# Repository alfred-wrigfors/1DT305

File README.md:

# 1DT305
Summer 2025 - Applied IoT

> [!NOTE]
> I, the author, have multiple years of experience in both embedded hardware design and software development. The level of complexity of this project is not reasonable for a beginner IoT-project!

## Introduction
With family living close to the Vikhög marina, there is the constant question wether or not the condition in/around the marina is appropriate for going swimming. It is mostly the water temperature and levels of wind that are of interest. Insight into the conditions in the marina would greatly increase the likelihood of spontaneous and enjoyable swims, while also helping to avoid unpleasant surprises - such as unexpected cold water or strong winds. Rather than relying on regional forecasts, a localized monitoring system would offer a much more accurate and timely solution.

This project aims to provide current and up-to-date temperature readings, for both the water and air, accross the marina and an overall wind speed and heading reading. The goal is to distribute 2-4 battery- and solar powered sensor-stations at the most popular areas for going swimming, communicating wirelessly with a base-station that is connected to the internet and sending the data to a remote server that provides the information (both current and historic) in a simple and intuitive web-interface.

## Goals and constraints
Some overall goals for the project:
 - Server / web interface containerized to run in a Docker container.
 - The base station and the mobile units should be electronically identical.
 - Hardware designed to be fully assebled by the PCB fab.
 - Be able to sustain one month (31 days) of operation without recharging the unit manually.
 - WiFi enabled.
 - USB-C (programming, serial debugging and power).
 - Temperature sensor (air and water)
 - Humidity sensor.
 - Light sensor (photoresisotr / phototransistor).
 - (Pressure sensor) [OPTIONAL]

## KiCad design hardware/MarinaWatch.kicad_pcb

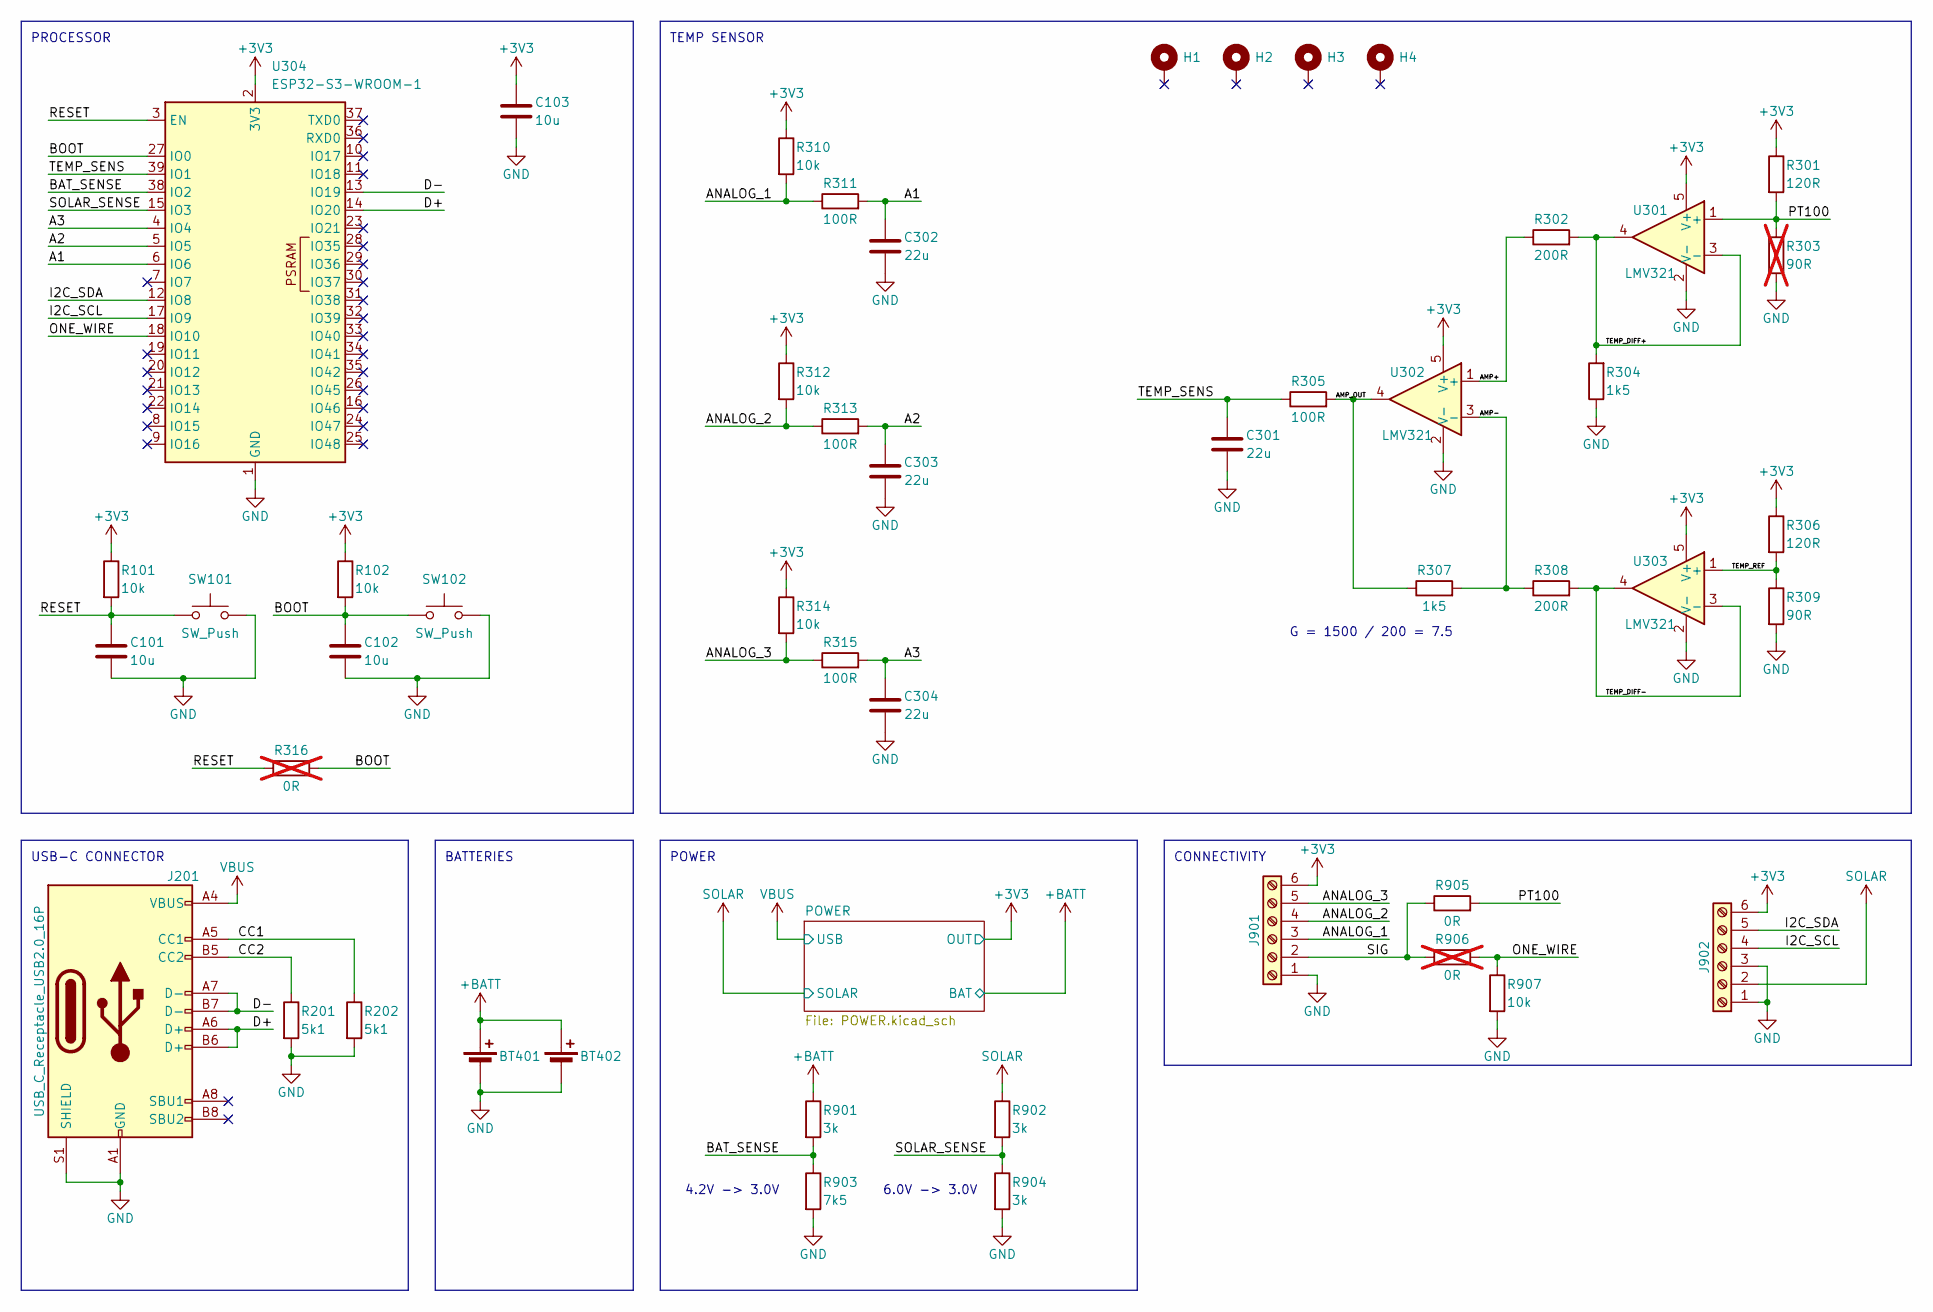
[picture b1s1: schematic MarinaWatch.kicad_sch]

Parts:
BT401, BT402: Battery_Cell; 18650
C101, C102, C103: 10u; C_0603_1608Metric_Pad1.08x0.95mm_HandSolder
C301, C302, C303, C304: 22u; C_0603_1608Metric_Pad1.08x0.95mm_HandSolder
H1, H2, H3, H4: MountingHole_Pad; MountingHole_3.2mm_M3_DIN965_Pad
J201: USB_C_Receptacle_USB2.0_16P; USB_C_Receptacle_G-Switch_GT-USB-7010ASV
J901, J902: Screw_Terminal_01x06; THT_SCREW_01x06_P5.08mm
R101, R102, R310, R312, R314, R907: 10k; R_0603_1608Metric_Pad0.98x0.95mm_HandSolder
R201, R202: 5k1; R_0603_1608Metric_Pad0.98x0.95mm_HandSolder
R301, R306: 120R; R_0603_1608Metric_Pad0.98x0.95mm_HandSolder
R302, R308: 200R; R_0603_1608Metric_Pad0.98x0.95mm_HandSolder
R303: 90R; R_0603_1608Metric_Pad0.98x0.95mm_HandSolder; not fitted
R304, R307: 1k5; R_0603_1608Metric_Pad0.98x0.95mm_HandSolder
R305, R311, R313, R315: 100R; R_0603_1608Metric_Pad0.98x0.95mm_HandSolder
R309: 90R; R_0603_1608Metric_Pad0.98x0.95mm_HandSolder
R316, R906: 0R; R_0603_1608Metric_Pad0.98x0.95mm_HandSolder; not fitted
R901, R902, R904: 3k; R_0603_1608Metric_Pad0.98x0.95mm_HandSolder
R903: 7k5; R_0603_1608Metric_Pad0.98x0.95mm_HandSolder
R905: 0R; R_0603_1608Metric_Pad0.98x0.95mm_HandSolder
SW101, SW102: SW_Push; BUTTON_SMD_3x4mm
U301, U302, U303: LMV321; SOT-23-5
U304: ESP32-S3-WROOM-1

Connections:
+3V3: C103.1, J901.6, J902.6, R101.1, R102.1, R301.1, R306.1, R310.1, R312.1, R314.1, U301.5 (V+), U302.5 (V+), U303.5 (V+), U304.2 (3V3); also elsewhere on the board
+BATT: BT401.1 (+), BT402.1 (+), R901.1; also elsewhere on the board
/A1: C302.1, R311.2, U304.6 (IO6)
/A2: C303.1, R313.2, U304.5 (IO5)
/A3: C304.1, R315.2, U304.4 (IO4)
/AMP+: R302.1, U302.1 (+)
/AMP-: R307.2, R308.1, U302.3 (-)
/AMP_OUT: R305.2, R307.1, U302.4
/ANALOG_1: J901.3, R310.2, R311.1
/ANALOG_2: J901.4, R312.2, R313.1
/ANALOG_3: J901.5, R314.2, R315.1
/BAT_SENSE: R901.2, R903.1, U304.38 (IO2)
/BOOT: C102.1, R102.2, R316.2, SW102.1, U304.27 (IO0)
/CC1: J201.A5 (CC1), R202.1
/CC2: J201.B5 (CC2), R201.1
/D+: J201.A6 (D+), J201.B6 (D+), U304.14 (IO20)
/D-: J201.A7 (D-), J201.B7 (D-), U304.13 (IO19)
/I2C_SCL: J902.4, U304.17 (IO9)
/I2C_SDA: J902.5, U304.12 (IO8)
/ONE_WIRE: R906.2, R907.1, U304.18 (IO10)
/PT100: R301.2, R303.1, R905.2, U301.1 (+)
/RESET: C101.1, R101.2, R316.1, SW101.1, U304.3 (EN)
/SIG: J901.2, R905.1, R906.1
/SOLAR_SENSE: R902.2, R904.1, U304.15 (IO3)
/TEMP_DIFF+: R302.2, R304.2, U301.3 (-), U301.4
/TEMP_DIFF-: R308.2, U303.3 (-), U303.4
/TEMP_REF: R306.2, R309.1, U303.1 (+)
/TEMP_SENS: C301.1, R305.1, U304.39 (IO1)
GND: BT401.2 (-), BT402.2 (-), C101.2, C102.2, C103.2, C301.2, C302.2, C303.2, C304.2, J201.A1 (GND), J201.A12 (GND), J201.B1 (GND), J201.B12 (GND), J201.S1 (SHIELD), J901.1, J902.1, J902.3, R201.2, R202.2, R303.2, R304.1, R309.2, R903.2, R904.2, R907.2, SW101.2, SW102.2, U301.2 (V-), U302.2 (V-), U303.2 (V-), U304.1 (GND), U304.40 (GND), U304.41 (GND); also elsewhere on the board
SOLAR: J902.2, R902.1; also elsewhere on the board
VBUS: J201.A4 (VBUS), J201.A9 (VBUS), J201.B4 (VBUS), J201.B9 (VBUS); also elsewhere on the board

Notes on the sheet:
BATTERIES
4.2V -> 3.0V
USB-C CONNECTOR
TEMP SENSOR
POWER
CONNECTIVITY
6.0V -> 3.0V
PROCESSOR
G = 1500 / 200 = 7.5

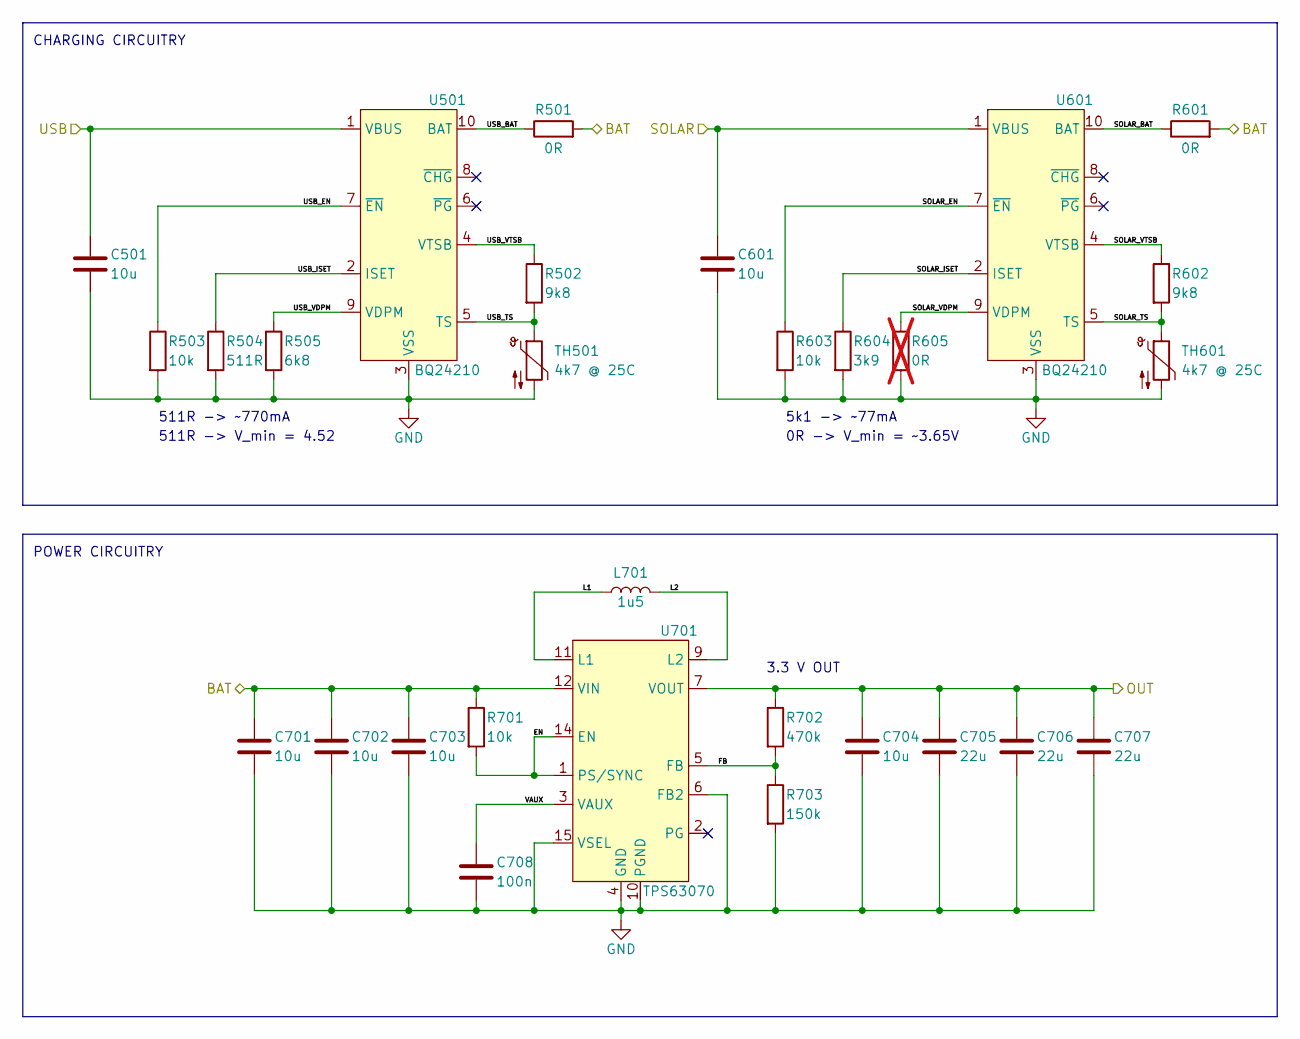
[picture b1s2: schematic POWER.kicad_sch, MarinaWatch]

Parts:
C501, C601, C701, C702, C703, C704: 10u; C_0603_1608Metric_Pad1.08x0.95mm_HandSolder
C705, C706, C707: 22u; C_0603_1608Metric_Pad1.08x0.95mm_HandSolder
C708: 100n; C_0603_1608Metric_Pad1.08x0.95mm_HandSolder
L701: 1u5; L_Wurth_WE-LQSH-2010
R501, R601: 0R; R_0603_1608Metric_Pad0.98x0.95mm_HandSolder
R502, R602: 9k8; R_0603_1608Metric_Pad0.98x0.95mm_HandSolder
R503, R603, R701: 10k; R_0603_1608Metric_Pad0.98x0.95mm_HandSolder
R504: 511R; R_0603_1608Metric_Pad0.98x0.95mm_HandSolder
R505: 6k8; R_0603_1608Metric_Pad0.98x0.95mm_HandSolder
R604: 3k9; R_0603_1608Metric_Pad0.98x0.95mm_HandSolder
R605: 0R; R_0603_1608Metric_Pad0.98x0.95mm_HandSolder; not fitted
R702: 470k; R_0603_1608Metric_Pad0.98x0.95mm_HandSolder
R703: 150k; R_0603_1608Metric_Pad0.98x0.95mm_HandSolder
TH501, TH601: 4k7 @ 25C; R_0603_1608Metric_Pad0.98x0.95mm_HandSolder
U501, U601: BQ24210; WSON-10
U701: TPS63070; VQFN-3.0x2.5

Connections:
+3V3: C704.1, C705.1, C706.1, C707.1, R702.1, U701.7 (VOUT), U701.8 (VOUT); also elsewhere on the board
+BATT: C701.1, C702.1, C703.1, R501.2, R601.2, R701.1, U701.12 (VIN), U701.13 (VIN); also elsewhere on the board
/POWER/EN: R701.2, U701.1 (PS/SYNC), U701.14 (EN)
/POWER/FB: R702.2, R703.1, U701.5 (FB)
/POWER/L1: L701.1, U701.11 (L1)
/POWER/L2: L701.2, U701.9 (L2)
/POWER/SOLAR_BAT: R601.1, U601.10 (BAT)
/POWER/SOLAR_EN: R603.1, U601.7 (~EN)
/POWER/SOLAR_ISET: R604.1, U601.2 (ISET)
/POWER/SOLAR_TS: R602.2, TH601.1, U601.5 (TS)
/POWER/SOLAR_VDPM: R605.1, U601.9 (VDPM)
/POWER/SOLAR_VTSB: R602.1, U601.4 (VTSB)
/POWER/USB_BAT: R501.1, U501.10 (BAT)
/POWER/USB_EN: R503.1, U501.7 (~EN)
/POWER/USB_ISET: R504.1, U501.2 (ISET)
/POWER/USB_TS: R502.2, TH501.1, U501.5 (TS)
/POWER/USB_VDPM: R505.1, U501.9 (VDPM)
/POWER/USB_VTSB: R502.1, U501.4 (VTSB)
/POWER/VAUX: C708.1, U701.3 (VAUX)
GND: C501.2, C601.2, C701.2, C702.2, C703.2, C704.2, C705.2, C706.2, C707.2, C708.2, R503.2, R504.2, R505.2, R603.2, R604.2, R605.2, R703.2, TH501.2, TH601.2, U501.3 (VSS), U601.3 (VSS), U701.4 (GND), U701.6 (FB2), U701.10 (PGND), U701.15 (VSEL); also elsewhere on the board
SOLAR: C601.1, U601.1 (VBUS); also elsewhere on the board
VBUS: C501.1, U501.1 (VBUS); also elsewhere on the board

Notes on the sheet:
3.3 V OUT
CHARGING CIRCUITRY
511R -> ~770mA
POWER CIRCUITRY
0R -> V_min = ~3.65V
511R -> V_min = 4.52
5k1 -> ~77mA

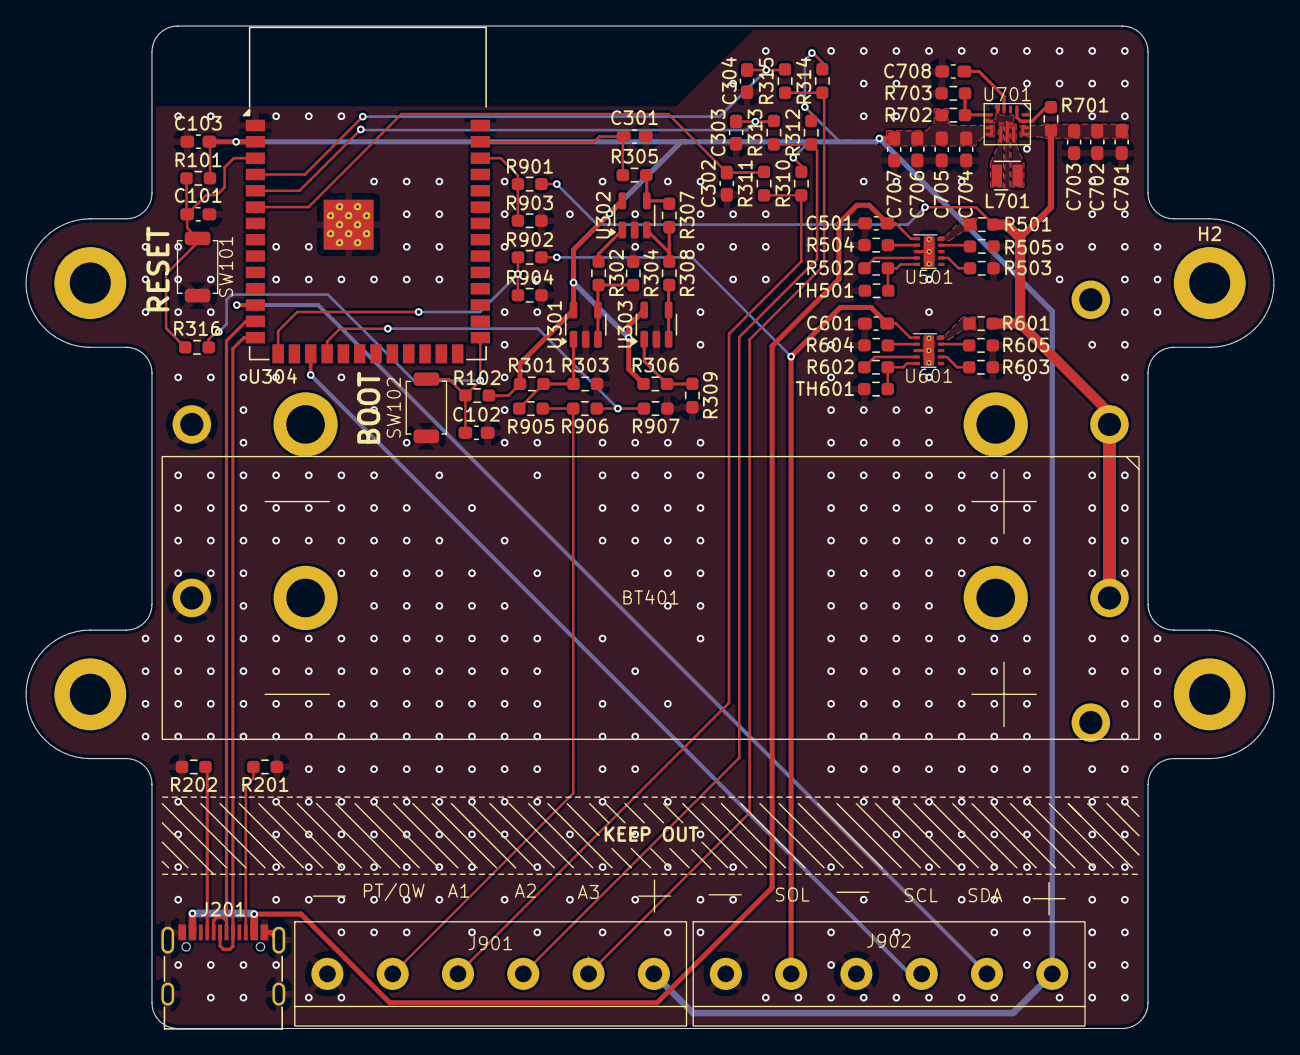
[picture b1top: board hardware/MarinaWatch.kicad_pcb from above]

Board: 2 copper layers, 97.1 x 78.0 mm, 78 parts (1 on the bottom side), 48 nets.

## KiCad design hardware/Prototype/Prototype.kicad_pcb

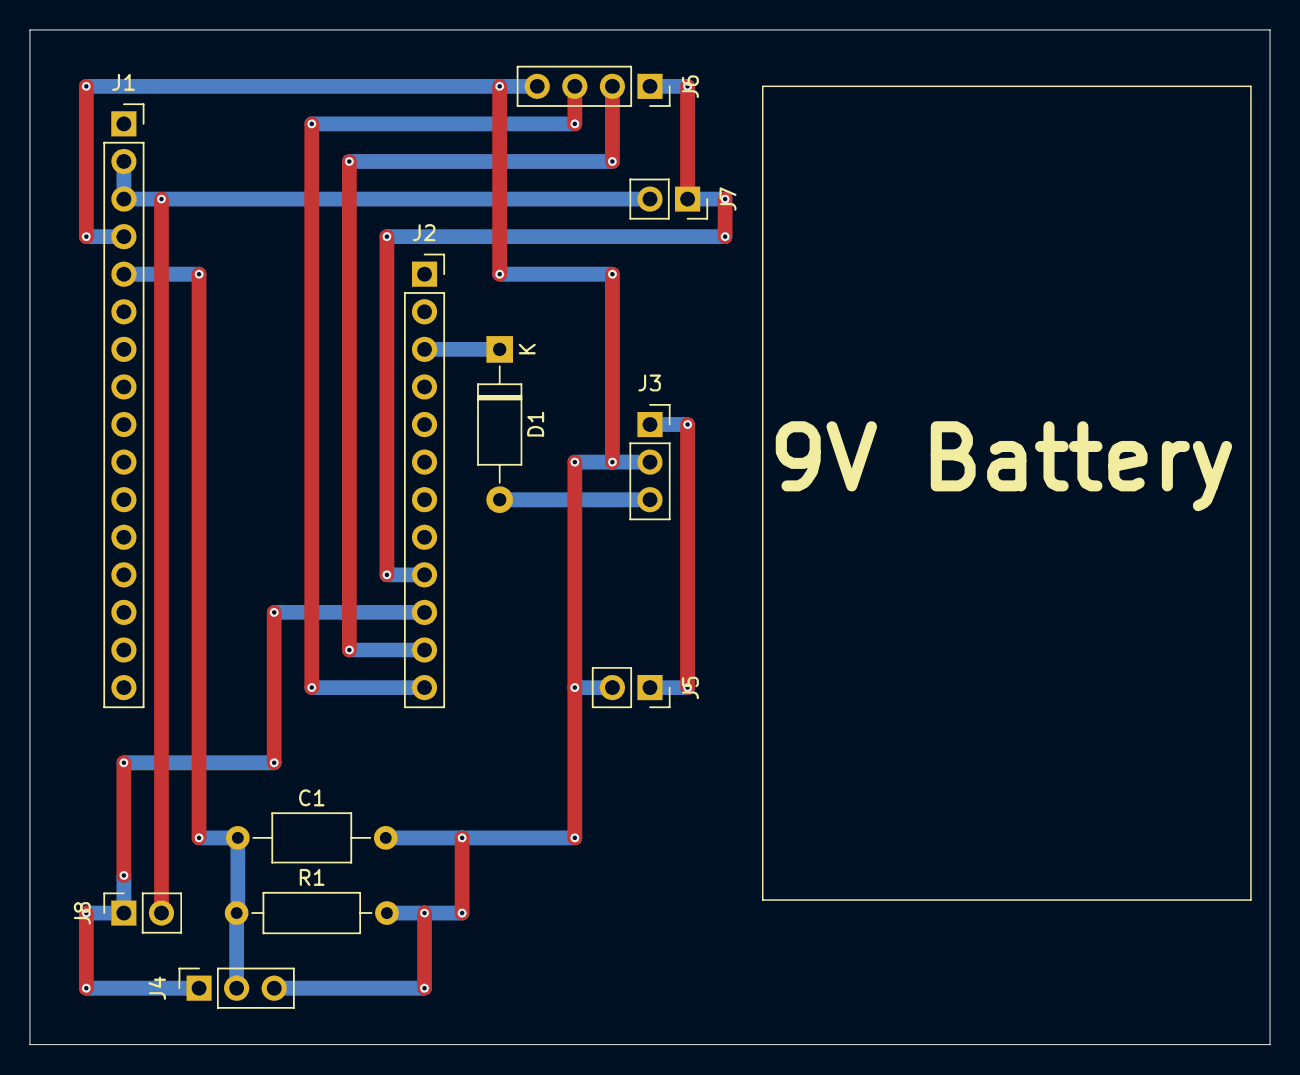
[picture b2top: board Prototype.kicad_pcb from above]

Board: 2 copper layers, 83.8 x 68.6 mm, 11 parts (0 on the bottom side), 10 nets.

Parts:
C1: 100n; C_Axial_L5.1mm_D3.1mm_P10.00mm_Horizontal
D1: D_Schottky; D_A-405_P10.16mm_Horizontal
J1: Conn_01x16_Socket; PinSocket_1x16_P2.54mm_Vertical
J2: Conn_01x12_Socket; PinSocket_1x12_P2.54mm_Vertical
J3, J4: Conn_01x03_Socket; PinSocket_1x03_P2.54mm_Vertical
J5, J7, J8: Conn_01x02_Socket; PinSocket_1x02_P2.54mm_Vertical
J6: Conn_01x04_Socket; PinSocket_1x04_P2.54mm_Vertical
R1: 220R; R_Axial_DIN0207_L6.3mm_D2.5mm_P10.16mm_Horizontal

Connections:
+3V3: J1.2, J1.3, J7.2, J8.2
+BATT: J3.1, J5.1
/PT_OUT: C1.1, J1.5, J4.2, R1.1
/PT_POWER: J2.10, J4.1, J8.1
/SCL: J2.11, J6.2
/SDA: J2.12, J6.3
/SHT_POWER: J2.9, J6.1, J7.1
GND: C1.2, J1.4, J3.2, J4.3, J5.2, J6.4, R1.2
unnamed: D1.2 (A), J3.3
VBUS: D1.1 (K), J2.3

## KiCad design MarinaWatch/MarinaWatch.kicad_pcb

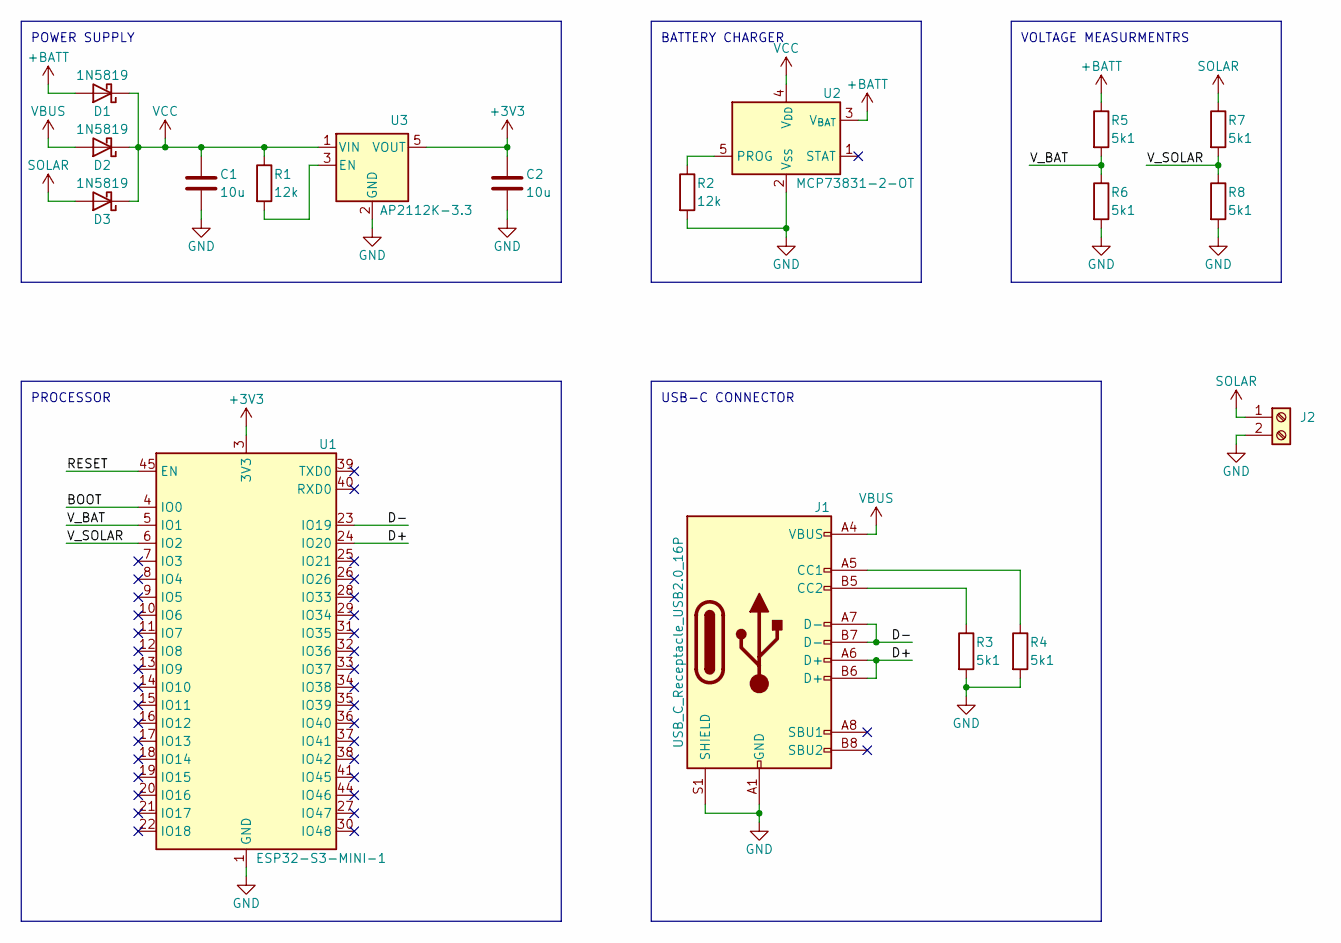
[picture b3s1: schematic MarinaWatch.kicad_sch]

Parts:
C1, C2: 10u; C_0603_1608Metric_Pad1.08x0.95mm_HandSolder
D1, D2, D3: 1N5819; D_SOD-123
J1: USB_C_Receptacle_USB2.0_16P; USB_C_Receptacle_G-Switch_GT-USB-7010ASV
J2: Screw_Terminal_01x02; TerminalBlock_MetzConnect_Type101_RT01602HBWC_1x02_P5.08mm_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
R1, R2: 12k; R_0603_1608Metric_Pad0.98x0.95mm_HandSolder
R3, R4, R5, R6, R7, R8: 5k1; R_0603_1608Metric_Pad0.98x0.95mm_HandSolder
U1: ESP32-S3-MINI-1; ESP32-S2-MINI-1
U2: MCP73831-2-OT; SOT-23-5
U3: AP2112K-3.3; SOT-23-5

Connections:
+3V3: C2.1, U1.3 (3V3), U3.5 (VOUT)
+BATT: D1.2 (A), R5.1, U2.3 (V_{BAT})
/BOOT: U1.4 (IO0)
/D+: J1.A6 (D+), J1.B6 (D+), U1.24 (IO20)
/D-: J1.A7 (D-), J1.B7 (D-), U1.23 (IO19)
/RESET: U1.45 (EN)
/V_BAT: R5.2, R6.1, U1.5 (IO1)
/V_SOLAR: R7.2, R8.1, U1.6 (IO2)
GND: C1.2, C2.2, J1.A1 (GND), J1.A12 (GND), J1.B1 (GND), J1.B12 (GND), J1.S1 (SHIELD), J2.2, R2.2, R3.2, R4.2, R6.2, R8.2, U1.1 (GND), U1.2 (GND), U1.42 (GND), U1.43 (GND), U1.46 (GND), U1.47 (GND), U1.48 (GND), U1.49 (GND), U1.50 (GND), U1.51 (GND), U1.52 (GND), U1.53 (GND), U1.54 (GND), U1.55 (GND), U1.56 (GND), U1.57 (GND), U1.58 (GND), U1.59 (GND), U1.60 (GND), U1.61 (GND), U1.62 (GND), U1.63 (GND), U1.64 (GND), U1.65 (GND), U2.2 (V_{SS}), U3.2 (GND)
unnamed: J1.A5 (CC1), R4.1
unnamed: J1.B5 (CC2), R3.1
unnamed: R2.1, U2.5 (PROG)
unnamed: R1.2, U3.3 (EN)
SOLAR: D3.2 (A), J2.1, R7.1
VBUS: D2.2 (A), J1.A4 (VBUS), J1.A9 (VBUS), J1.B4 (VBUS), J1.B9 (VBUS)
VCC: C1.1, D1.1 (K), D2.1 (K), D3.1 (K), R1.1, U2.4 (V_{DD}), U3.1 (VIN)

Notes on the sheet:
VOLTAGE MEASURMENTRS
USB-C CONNECTOR
PROCESSOR
POWER SUPPLY
BATTERY CHARGER

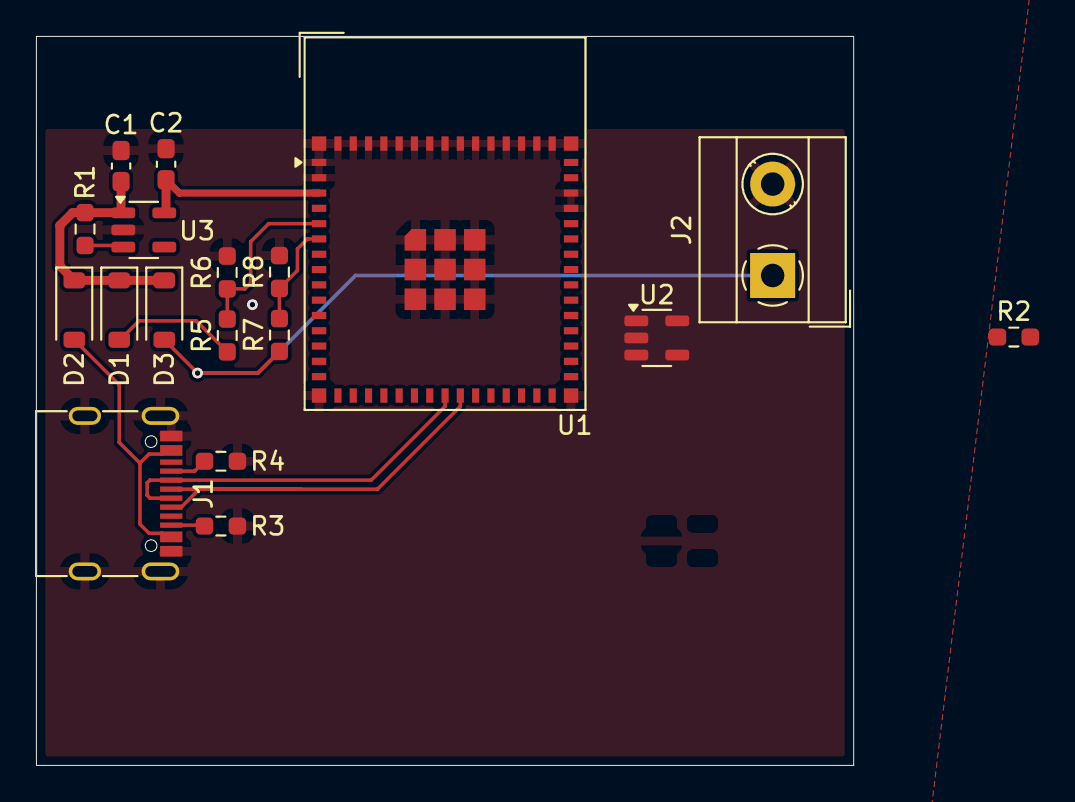
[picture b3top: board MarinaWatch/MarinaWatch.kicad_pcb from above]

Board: 2 copper layers, 45.4 x 40.5 mm, 18 parts (0 on the bottom side), 14 nets.

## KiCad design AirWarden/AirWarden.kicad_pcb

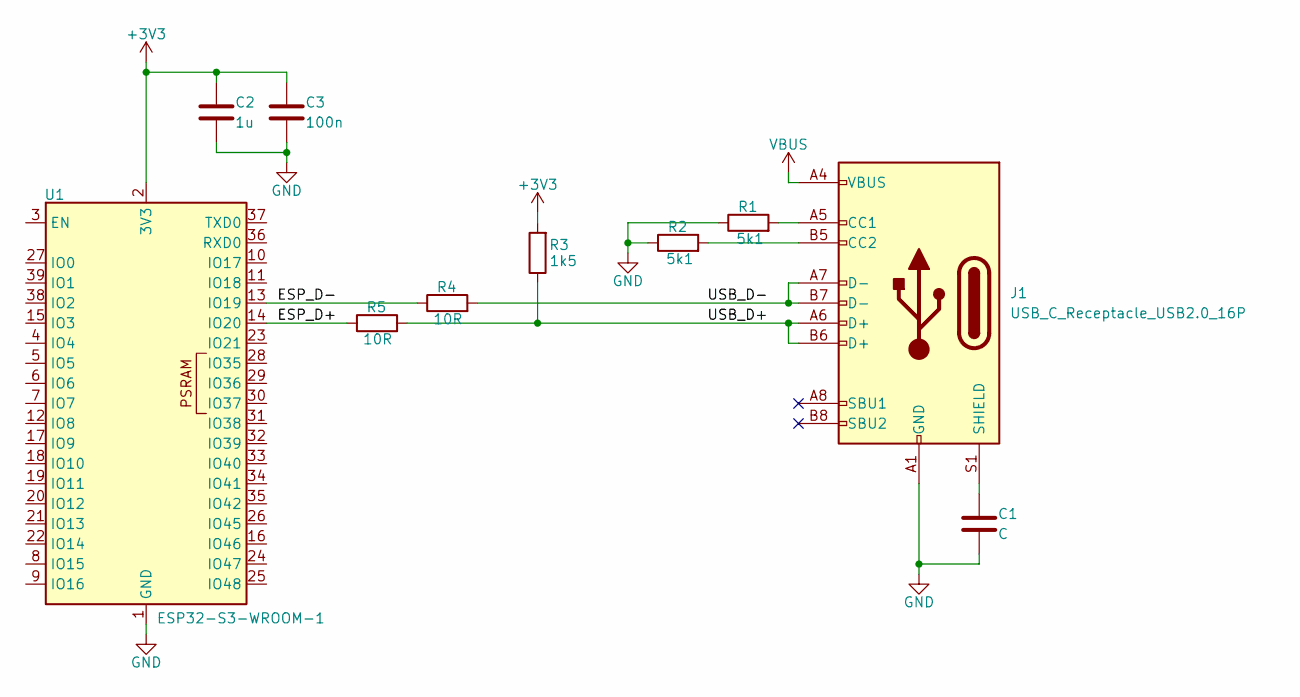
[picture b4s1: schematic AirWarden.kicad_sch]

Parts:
C1: C; C_0603_1608Metric_Pad1.08x0.95mm_HandSolder
C2: 1u; C_0603_1608Metric_Pad1.08x0.95mm_HandSolder
C3: 100n; C_0603_1608Metric_Pad1.08x0.95mm_HandSolder
J1: USB_C_Receptacle_USB2.0_16P; USB_C_Receptacle_G-Switch_GT-USB-7010ASV
R1, R2: 5k1; R_0603_1608Metric_Pad0.98x0.95mm_HandSolder
R3: 1k5; R_0603_1608Metric_Pad0.98x0.95mm_HandSolder
R4, R5: 10R; R_0603_1608Metric_Pad0.98x0.95mm_HandSolder
U1: ESP32-S3-WROOM-1

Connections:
+3V3: C2.1, C3.1, R3.2, U1.2 (3V3)
/ESP_D+: R5.1, U1.14 (IO20)
/ESP_D-: R4.1, U1.13 (IO19)
/USB_D+: J1.A6 (D+), J1.B6 (D+), R3.1, R5.2
/USB_D-: J1.A7 (D-), J1.B7 (D-), R4.2
GND: C1.2, C2.2, C3.2, J1.A1 (GND), J1.A12 (GND), J1.B1 (GND), J1.B12 (GND), R1.1, R2.1, U1.1 (GND), U1.40 (GND), U1.41 (GND)
unnamed: J1.A5 (CC1), R1.2
unnamed: J1.B5 (CC2), R2.2
unnamed: C1.1, J1.S1 (SHIELD)
VBUS: J1.A4 (VBUS), J1.A9 (VBUS), J1.B4 (VBUS), J1.B9 (VBUS)

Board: 2 copper layers, 10 parts (0 on the bottom side), 10 nets, no tracks yet.

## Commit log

2025-04-29 iNITIAL STRUCTURE OF sw
2025-04-29 Added initial HW
2025-04-29 Start of readme and test of alerts
2025-04-29 Alert test
2025-04-29 Fixed alert abour complexity
2025-04-29 grammar
2025-04-29 More readme
2025-04-29 New backup
2025-05-17 Added python venv to .gitignore
2025-05-17 Added python env to .gitignore
2025-05-17 Started with a simple battery simulation with solar
2025-05-18 More tuning of parameter
2025-05-22 Changed project
2025-05-23 Finished USB hardware. Started power supply.
2025-05-25 Structure power supply chain
2025-06-12 Restarted HW and started testing ESP32 WiFi
2025-06-16 2.54mm THT prototype board
2025-06-21 Working prototype
2025-06-30 Start server side software
2025-06-30 Script to compile all separate sections of the reports into a single document
2025-06-30 First parts of the report, not finished
2025-06-30 First compiled report
2025-07-01 Started with HW
2025-07-02 Main website
2025-07-02 Add styles and doc structure for html
2025-07-02 Add chart dependencies (have been used before)
2025-07-02 All needed sections?
2025-07-02 Remove old code
2025-07-02 Define constants
2025-07-02 Center body (and text)
2025-07-02 Fix viewport issues on mobile
2025-07-02 Scale container (main div) and populate full screen
2025-07-02 Style text (font, size and color)
2025-07-02 Add nice box around information
2025-07-02 Add local library and update chart one every seconds with mock data
2025-07-02 Working site, with updating chart
2025-07-02 Update current condidtions as well.
2025-07-03 Restructure for docker compose and first working iteration of database
2025-07-04 Misc
2025-07-04 time
2025-07-06 Working on analog sensor
2025-07-06 Do not track .env
2025-07-06 MQTT communication not working yet
2025-07-07 Working API, some cleanup to be done
2025-07-07 Working SAPI and web page for http
2025-07-07 Full implemntation with state mashine. Not using deep sleep yet
2025-07-07 Constants
2025-07-07 Fix copy-paste issue for voltage and soc
2025-07-07 Added deep sleep - tested and working
2025-07-07 Calibrated voltage measurment against miltimeter
2025-07-08 Working on API handling
2025-07-09 Finished schematics for presentation
2025-07-09 Refactor to make the code easier to read
2025-07-09 Change format of hidded credentials
2025-07-22 Working on production version
2025-07-27 Restructure resistor calculations
2025-07-27 Added wheatstone bridge, battery chargers and 3v3 power supply
2025-07-27 Added more accurate value to simulation
2025-07-27 Closed project
2025-07-27 Started with calculations for amplifier stage
2025-07-28 Started with footprints and layout
2025-07-29 Working on power circuitry layout
2025-07-30 Layout almost finished (missing NTCs and Buttons)
2025-07-30 Moved python scripts
2025-07-30 Early portfoliofile
2025-07-30 Remove old containers
2025-08-02 First draft of HW and moved scripts
2025-08-02 Added NTCs
2025-08-02 Recond draft of HW
2025-08-02 Renamed portfolio info-file
2025-08-02 Changed to yaml format
2025-08-03 Calculating values
